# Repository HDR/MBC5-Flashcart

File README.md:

## Make sure you read the License (Attribution-NonCommercial-ShareAlike 4.0 International)

If you want to support me for free (and get 5 USD in new user credit) you can use my PCBWay [Referral link](https://www.pcbway.com/setinvite.aspx?inviteid=388393) when signing up on PCBWay

**Make sure you read the License!**

**BOM:**

| Reference | Part Number | Description |
|-|-|-|
| U1 | MBC5 | Harvest from original cartridge |
| U2 | [MBM29F033C/AM29F032 (4MB)](https://www.aliexpress.com/item/32711470187.html) | 4MB Flash (TSOP-40) |
| U3 | [FM18W08-SG](https://www.aliexpress.com/item/1005002024061036.html) | 256Kb FRAM (SOIC-28) |
| U4 | [74LVC1G332GV,125](https://www.nexperia.com/products/analog-logic-ics/control-logic/gates/or-gates/74LVC1G332GV.html) | 3-Input OR Gate (TSOP-6) |
| C1, C2, C3, C4, C5 | [CC0603KRX7R7BB104](https://lcsc.com/product-detail/Multilayer-Ceramic-Capacitors-MLCC-SMD-SMT_YAGEO-CC0603KRX7R7BB104_C108079.html) | 100nF 0603 16V |
| R1 | [RC0603JR-0710KL](https://lcsc.com/product-detail/Chip-Resistor-Surface-Mount_YAGEO-RC0603JR-0710KL_C99198.html) | 10kΩ 0603 |
| R2 | [RC0603JR-0730KL](https://lcsc.com/product-detail/Chip-Resistor-Surface-Mount_YAGEO-RC0603JR-0730KL_C113302.html) | 30kΩ 0603 |
| R3 | [RS-03K150JT](https://lcsc.com/product-detail/Chip-Resistor-Surface-Mount_FH-Guangdong-Fenghua-Advanced-Tech-RS-03K150JT_C187891.html) | 15Ω 0603 |
| D1 | [SD103AW](https://lcsc.com/product-detail/Schottky-Barrier-Diodes-SBD_Guangdong-Hottech-SD103AW_C181204.html) | SOD-123 |
| Q1 | [BC817-40,215](https://www.nexperia.com/products/bipolar-transistors/general-purpose-and-low-vcesat-bipolar-transistors/single-bipolar-transistors/single-bipolar-transistors-100-v/BC817-40.html) | SOT-23 |
| M1 | [Vibration Motor](https://www.aliexpress.com/item/32787320737.html) |  |
| Switch | [SP3T](https://www.aliexpress.com/item/32759020917.html) or CUS-13TB | 3 Position SP3T Switch |

*Parts & Links are suggestions, feel free to use different components as long as they have the same specs*

[Interactive BOM](https://martinrefseth.com/ibom/MBC5-Flashcart.html)

Makes use of [djedditt's](https://github.com/djedditt/s) [gamepak footprint](https://github.com/djedditt/kicad-gamepaks)

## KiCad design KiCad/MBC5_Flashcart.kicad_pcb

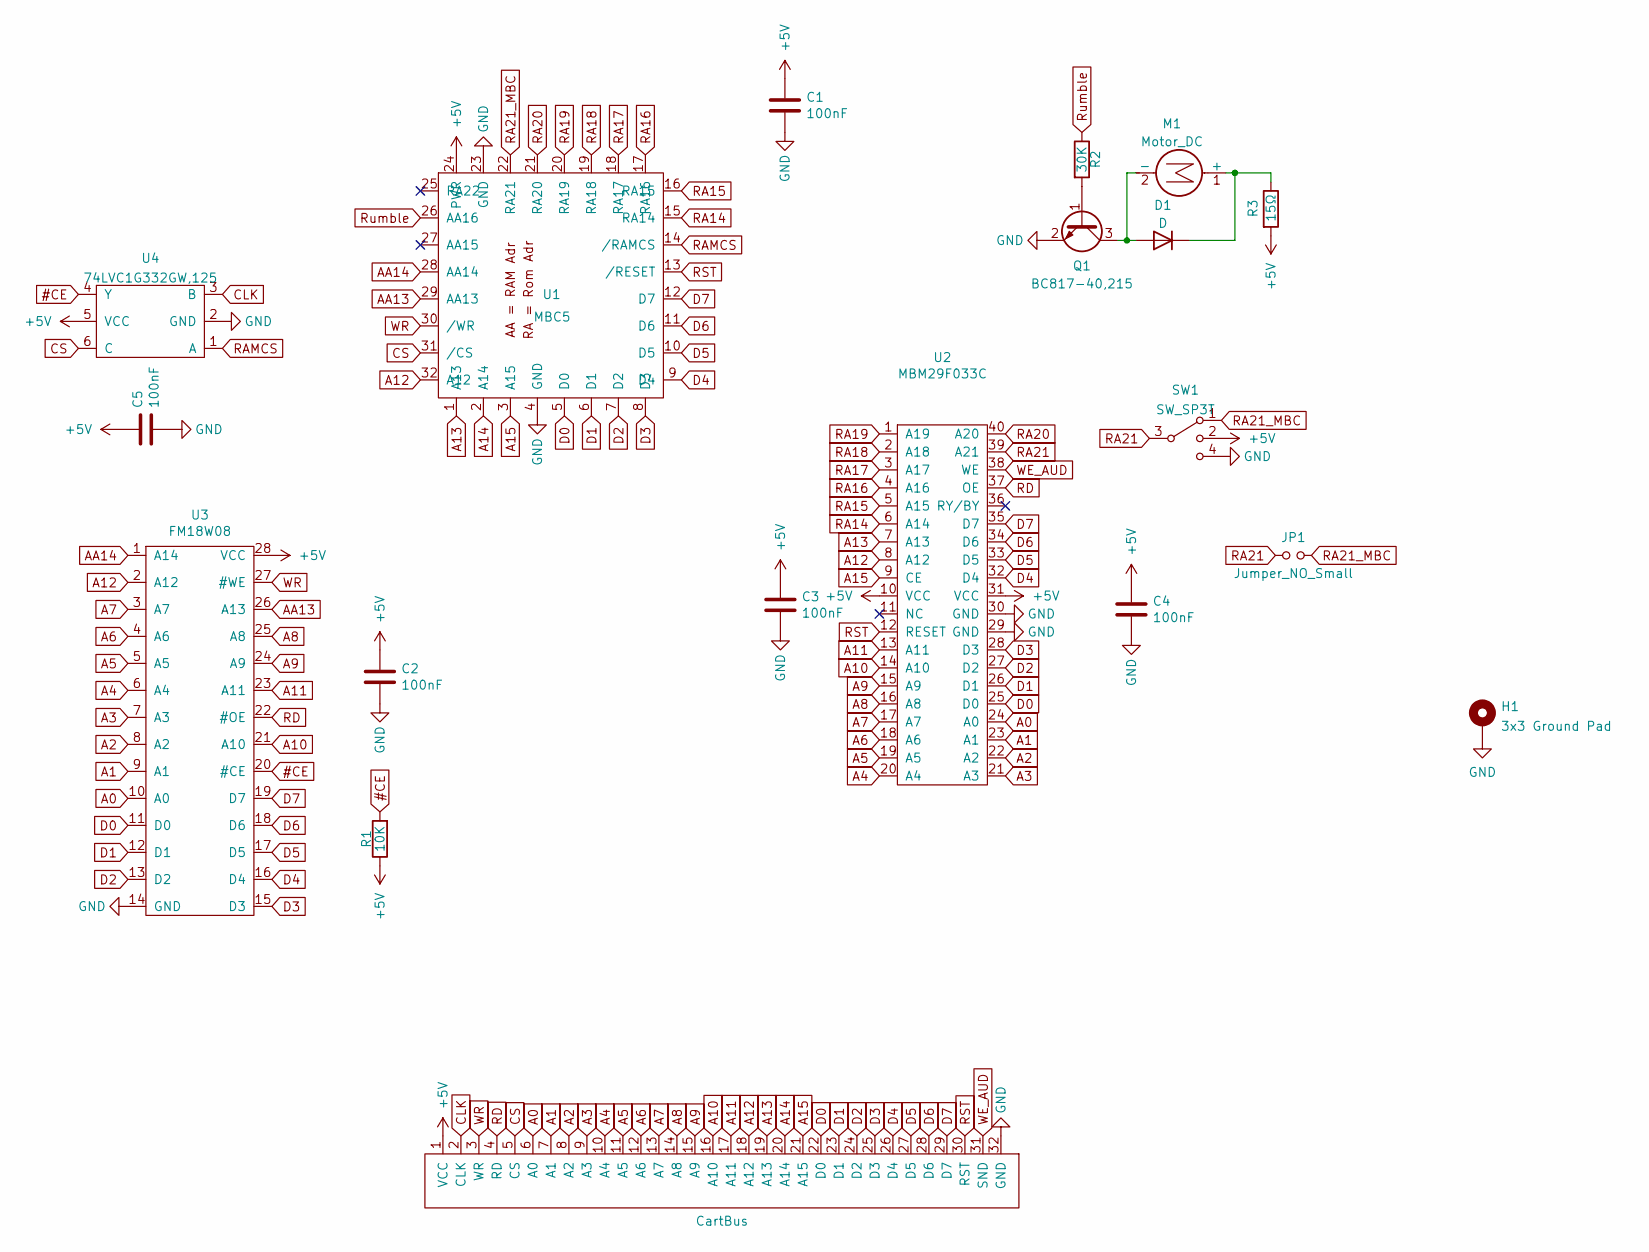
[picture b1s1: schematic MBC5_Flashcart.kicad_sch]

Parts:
C1, C2, C3, C4, C5: 100nF; C_0603_1608Metric
D1: D; D_SOD-123
H1: 3x3 Ground Pad; Nintendo_3x3_GNDPad
J0: CartBus; GB_Cartridge
JP1: Jumper_NO_Small; SolderJumper-2_P1.3mm_Open_RoundedPad1.0x1.5mm
M1: Motor_DC; ANDA-T1035
Q1: BC817-40,215; SOT-23
R1: 10K; R_0603_1608Metric
R2: 30K; R_0603_1608Metric
R3: 15Ω; R_0603_1608Metric
SW1: SW_SP3T; CUS-13TB-Aliex SP3T
U1: MBC5; LQFP-32_7x7mm_P0.8mm
U2: MBM29F033C; TSOP-I-40_18.4x10mm_P0.5mm
U3: FM18W08; SOIC-28W_7.5x17.9mm_P1.27mm
U4: 74LVC1G332GW,125; TSOP-6_1.65x3.05mm_P0.95mm

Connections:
#CE: R1.2, U3.20 (#CE), U4.4 (Y)
+5V: C1.1, C2.1, C3.1, C4.1, C5.1, J0.1 (VCC), R1.1, R3.2, SW1.2, U1.24 (PWR), U2.10 (VCC), U2.31 (VCC), U3.28 (VCC), U4.5 (VCC)
A0: J0.6 (A0), U2.24 (A0), U3.10 (A0)
A1: J0.7 (A1), U2.23 (A1), U3.9 (A1)
A2: J0.8 (A2), U2.22 (A2), U3.8 (A2)
A3: J0.9 (A3), U2.21 (A3), U3.7 (A3)
A4: J0.10 (A4), U2.20 (A4), U3.6 (A4)
A5: J0.11 (A5), U2.19 (A5), U3.5 (A5)
A6: J0.12 (A6), U2.18 (A6), U3.4 (A6)
A7: J0.13 (A7), U2.17 (A7), U3.3 (A7)
A8: J0.14 (A8), U2.16 (A8), U3.25 (A8)
A9: J0.15 (A9), U2.15 (A9), U3.24 (A9)
A10: J0.16 (A10), U2.14 (A10), U3.21 (A10)
A11: J0.17 (A11), U2.13 (A11), U3.23 (A11)
A12: J0.18 (A12), U1.32 (A12), U2.8 (A12), U3.2 (A12)
A13: J0.19 (A13), U1.1 (A13), U2.7 (A13)
A14: J0.20 (A14), U1.2 (A14)
A15: J0.21 (A15), U1.3 (A15), U2.9 (CE)
AA13: U1.29 (AA13), U3.26 (A13)
AA14: U1.28 (AA14), U3.1 (A14)
CLK: J0.2 (CLK~), U4.3 (B)
CS: J0.5 (CS), U1.31 (/CS), U4.6 (C)
D0: J0.22 (D0), U1.5 (D0), U2.25 (D0), U3.11 (D0)
D1: J0.23 (D1), U1.6 (D1), U2.26 (D1), U3.12 (D1)
D2: J0.24 (D2), U1.7 (D2), U2.27 (D2), U3.13 (D2)
D3: J0.25 (D3), U1.8 (D3), U2.28 (D3), U3.15 (D3)
D4: J0.26 (D4), U1.9 (D4), U2.32 (D4), U3.16 (D4)
D5: J0.27 (D5), U1.10 (D5), U2.33 (D5), U3.17 (D5)
D6: J0.28 (D6), U1.11 (D6), U2.34 (D6), U3.18 (D6)
D7: J0.29 (D7), U1.12 (D7), U2.35 (D7), U3.19 (D7)
GND: C1.2, C2.2, C3.2, C4.2, C5.2, H1.1, J0.32 (GND), Q1.2 (E), SW1.4, U1.4 (GND), U1.23 (GND), U2.29 (GND), U2.30 (GND), U3.14 (GND), U4.2 (GND); also elsewhere on the board
unnamed: D1.1 (K), M1.1 (+), R3.1
unnamed: D1.2 (A), M1.2 (-), Q1.3 (C)
unnamed: Q1.1 (B), R2.2
RA14: U1.15 (RA14), U2.6 (A14)
RA15: U1.16 (RA15), U2.5 (A15)
RA16: U1.17 (RA16), U2.4 (A16)
RA17: U1.18 (RA17), U2.3 (A17)
RA18: U1.19 (RA18), U2.2 (A18)
RA19: U1.20 (RA19), U2.1 (A19)
RA20: U1.21 (RA20), U2.40 (A20)
RA21: JP1.1, SW1.3, U2.39 (A21)
RA21_MBC: JP1.2, SW1.1, U1.22 (RA21)
RAMCS: U1.14 (/RAMCS), U4.1 (A)
RD: J0.4 (RD), U2.37 (OE), U3.22 (#OE)
RST: J0.30 (RST), U1.13 (/RESET), U2.12 (RESET)
Rumble: R2.1, U1.26 (AA16)
WE_AUD: J0.31 (SND), U2.38 (WE)
WR: J0.3 (WR), U1.30 (/WR), U3.27 (#WE)

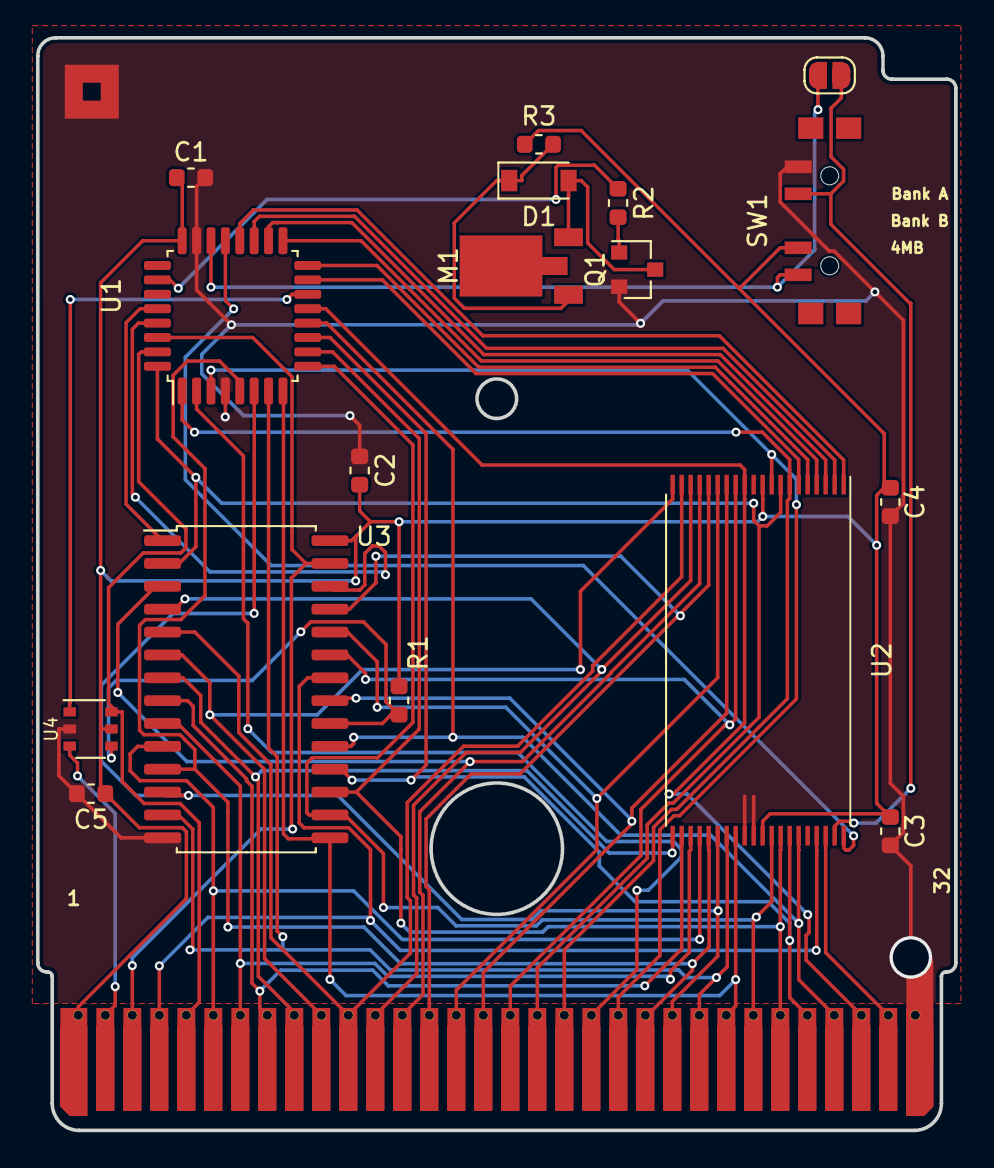
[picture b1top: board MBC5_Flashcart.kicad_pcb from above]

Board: 2 copper layers, 51.0 x 60.7 mm, 20 parts (1 on the bottom side), 49 nets.

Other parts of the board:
A**: June; 08 August

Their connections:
GND: A**.1; also elsewhere on the board

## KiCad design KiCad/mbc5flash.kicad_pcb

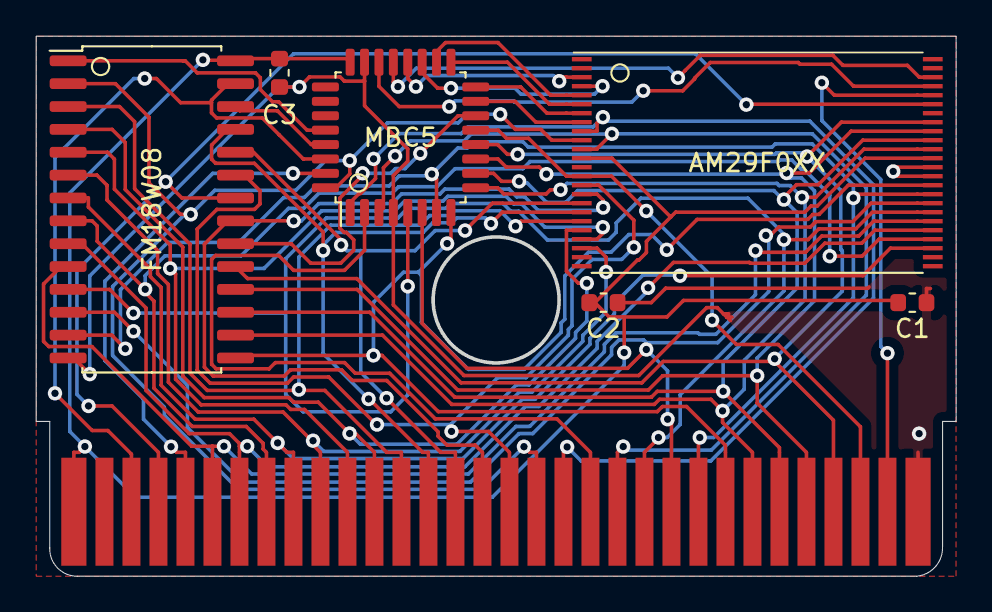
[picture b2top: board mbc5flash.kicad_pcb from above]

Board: 2 copper layers, 50.9 x 29.8 mm, 7 parts (0 on the bottom side), 42 nets.

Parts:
AM29F0XX: AM29F016; TSOP-I-48_18.4x12mm_P0.5mm
C1, C2, C3: 0.1uF; C_0603_1608Metric
FM18W08: FM18W08; SOIC-28W_7.5x17.9mm_P1.27mm
MBC5: MBC5; LQFP-32_7x7mm_P0.8mm
U0: CartBus; GBBus

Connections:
A0: AM29F0XX.30, FM18W08.10, U0.6
A1: AM29F0XX.29, FM18W08.9, U0.7
A2: AM29F0XX.28, FM18W08.8, U0.8
A3: AM29F0XX.27, FM18W08.7, U0.9
A4: AM29F0XX.22, FM18W08.6, U0.10
A5: AM29F0XX.21, FM18W08.5, U0.11
A6: AM29F0XX.20, FM18W08.4, U0.12
A7: AM29F0XX.19, FM18W08.3, U0.13
A8: AM29F0XX.18, FM18W08.25, U0.14
A9: AM29F0XX.17, FM18W08.24, U0.15
A10: AM29F0XX.16, FM18W08.21, U0.16
A11: AM29F0XX.15, FM18W08.23, U0.17
A12: AM29F0XX.10, FM18W08.2, MBC5.32, U0.18
A13: AM29F0XX.9, MBC5.1, U0.19
A14: MBC5.2, U0.20
A15: AM29F0XX.11, MBC5.3, U0.21
AA13: FM18W08.26, MBC5.29
AA14: FM18W08.1, MBC5.28
CS: MBC5.31, U0.5
D0: AM29F0XX.31, FM18W08.11, MBC5.5, U0.22
D1: AM29F0XX.32, FM18W08.12, MBC5.6, U0.23
D2: AM29F0XX.33, FM18W08.13, MBC5.7, U0.24
D3: AM29F0XX.34, FM18W08.15, MBC5.8, U0.25
D4: AM29F0XX.38, FM18W08.16, MBC5.9, U0.26
D5: AM29F0XX.39, FM18W08.17, MBC5.10, U0.27
D6: AM29F0XX.40, FM18W08.18, MBC5.11, U0.28
D7: AM29F0XX.41, FM18W08.19, MBC5.12, U0.29
GND: AM29F0XX.35, AM29F0XX.36, C1.1, C2.1, C3.1, FM18W08.14, MBC5.4, MBC5.23, U0.32
RA14: AM29F0XX.8, MBC5.15
RA15: AM29F0XX.7, MBC5.16
RA16: AM29F0XX.6, MBC5.17
RA17: AM29F0XX.5, MBC5.18
RA18: AM29F0XX.4, MBC5.19
RA19: AM29F0XX.3, MBC5.20
RA20: AM29F0XX.46, MBC5.21
RA21: AM29F0XX.45, MBC5.22
RESET: AM29F0XX.14, MBC5.13, U0.30
VCC: AM29F0XX.12, AM29F0XX.37, C1.2, C2.2, C3.2, FM18W08.28, MBC5.24, U0.1
WE_AUDIO: AM29F0XX.44, U0.31
\RAMCS: FM18W08.20, MBC5.14
\RD: AM29F0XX.43, FM18W08.22, U0.4
\WR: FM18W08.27, MBC5.30, U0.3

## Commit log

2020-08-28 add kicad files
2020-08-28 add readme and sponsor
2021-09-09 Add files
2022-04-28 Update to V2
2022-08-27 Release V3
2022-08-27 Remove R4
